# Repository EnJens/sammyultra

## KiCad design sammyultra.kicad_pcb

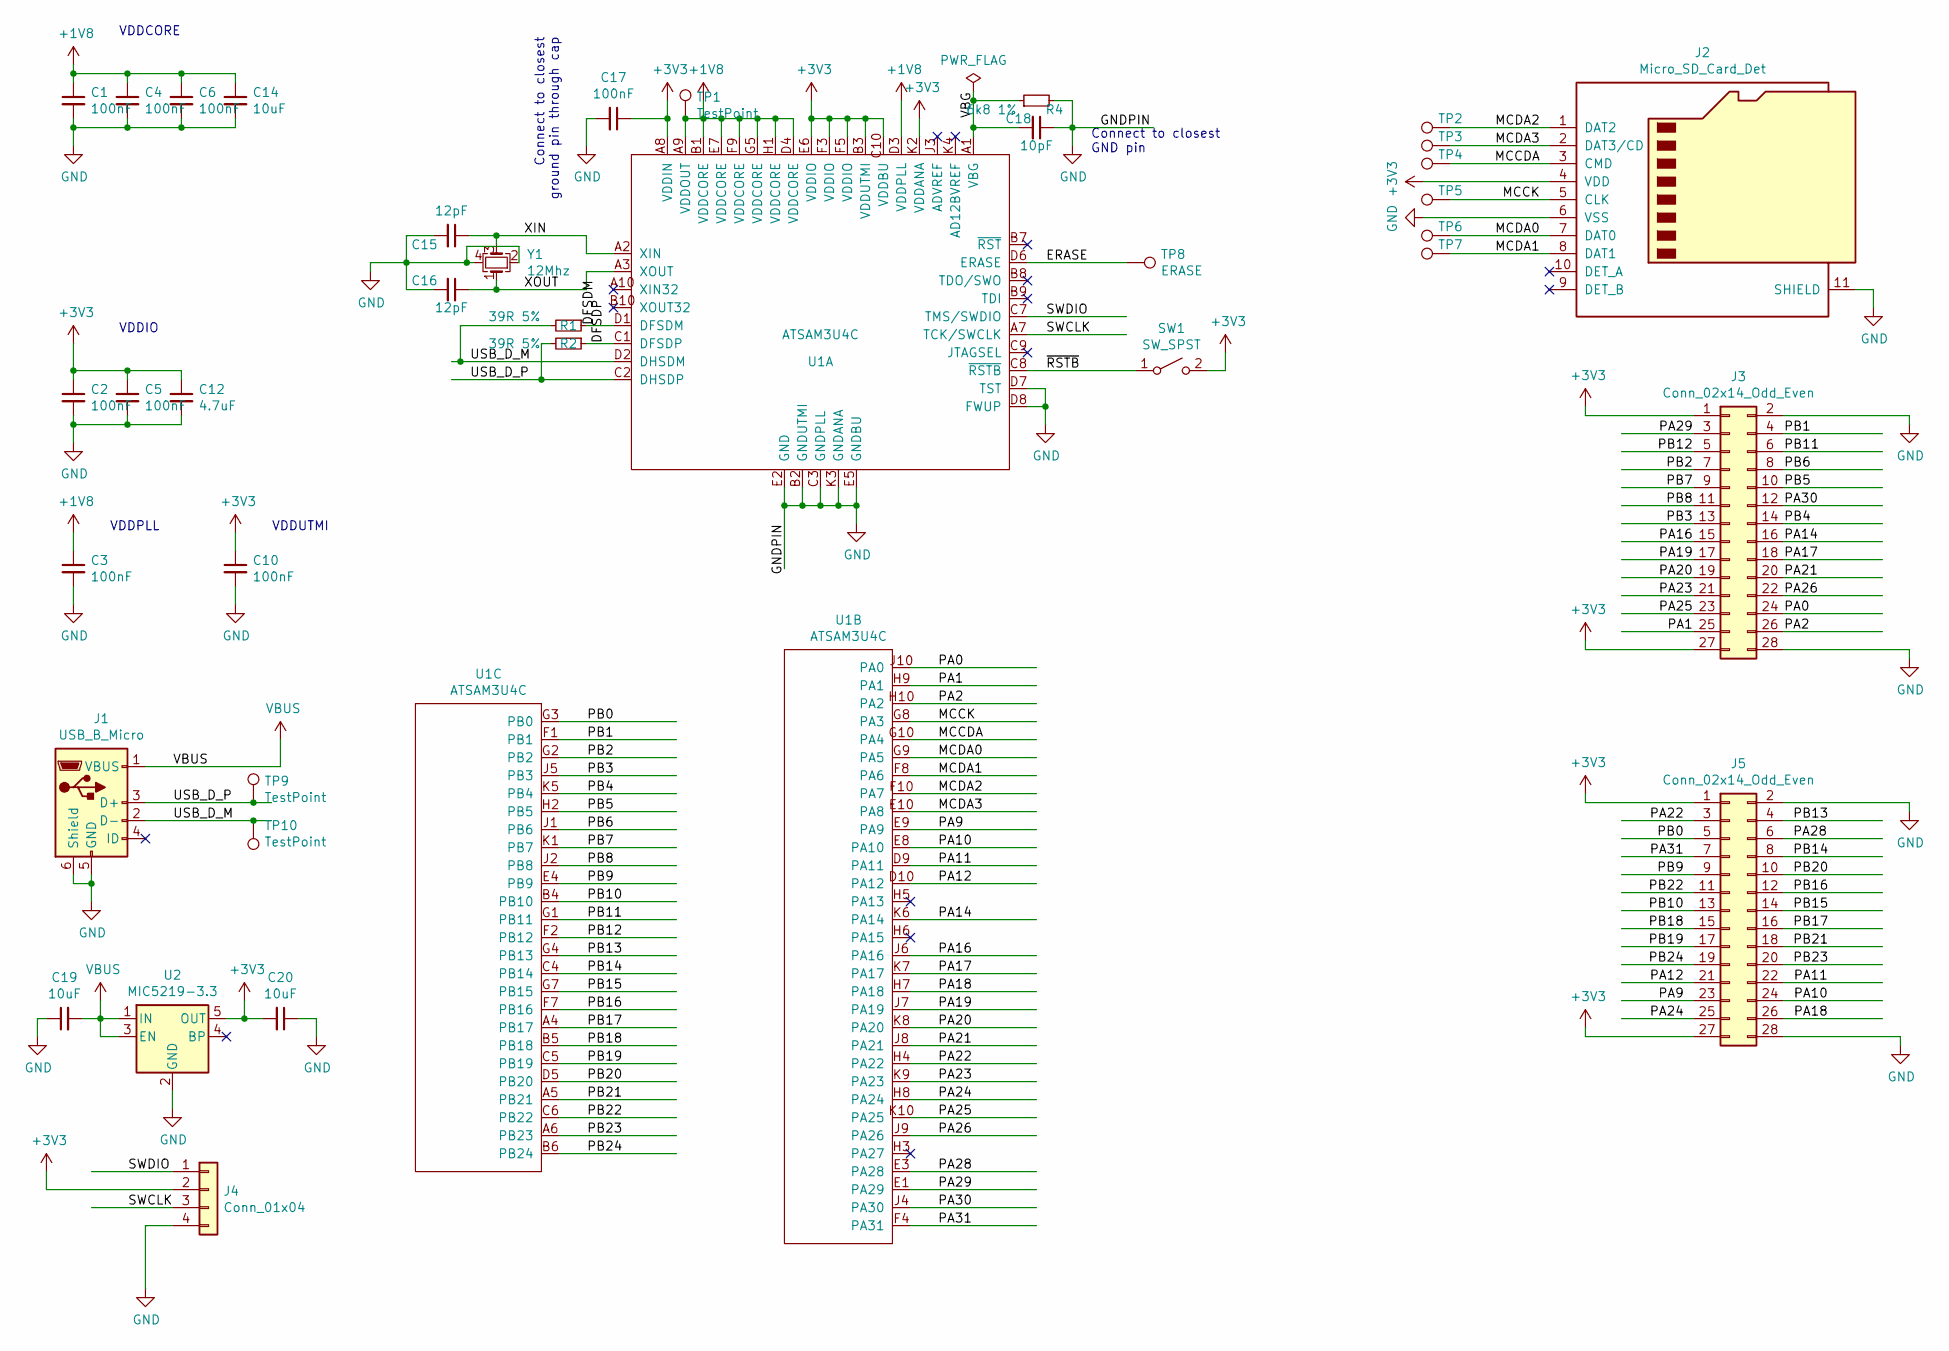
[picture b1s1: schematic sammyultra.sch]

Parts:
C1, C2, C3, C4, C5, C6, C10, C17: 100nF; C_0402_1005Metric
C12: 4.7uF; C_0603_1608Metric
C14, C19, C20: 10uF; C_0603_1608Metric
C15, C16: 12pF; C_0603_1608Metric
C18: 10pF; C_0402_1005Metric
J1: USB_B_Micro; USB_Micro-B_Molex-105017-0001
J2: Micro_SD_Card_Det; MOLEX_104031-0811
J3, J5: Conn_02x14_Odd_Even; PinHeader_2x14_P2.54mm_Vertical
J4: Conn_01x04; PinHeader_1x04_P1.27mm_Vertical
R1, R2: 39R 5%; R_0402_1005Metric
R4: 6k8 1%; R_0402_1005Metric
SW1: SW_SPST; SW_SPST_FSMSM
TP1, TP9, TP10: TestPoint; TestPoint_THTPad_D1.0mm_Drill0.5mm
TP2: MCDA2; TestPoint_Pad_D1.0mm
TP3: MCDA3; TestPoint_Pad_D1.0mm
TP4: MCCDA; TestPoint_Pad_D1.0mm
TP5: MCCK; TestPoint_Pad_D1.0mm
TP6: MCDA0; TestPoint_Pad_D1.0mm
TP7: MCDA1; TestPoint_Pad_D1.0mm
TP8: ERASE; TestPoint_THTPad_D1.0mm_Drill0.5mm
U1: ATSAM3U4C; BGA-100_10x10_9.0x9.0mm_Pitch_0.8mm_NSMD
U2: MIC5219-3.3; SOT-23-5
Y1: 12Mhz; Crystal_SMD_2520-4Pin_2.5x2.0mm

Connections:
+1V8: C1.1, C3.1, C4.1, C6.1, C14.1, TP1.1, U1.A9 (VDDOUT), U1.B1 (VDDCORE), U1.D3 (VDDPLL), U1.D4 (VDDCORE), U1.E7 (VDDCORE), U1.F9 (VDDCORE), U1.G5 (VDDCORE), U1.H1 (VDDCORE)
+3V3: C2.1, C5.1, C10.1, C12.1, C17.1, C20.2, J2.4 (VDD), J3.1, J3.27, J4.2, J5.1, J5.27, SW1.2 (B), U1.A8 (VDDIN), U1.B3 (VDDUTMI), U1.C10 (VDDBU), U1.E6 (VDDIO), U1.F3 (VDDIO), U1.F5 (VDDIO), U1.K2 (VDDANA), U2.5 (OUT)
/DFSDM: R1.1, U1.D1 (DFSDM)
/DFSDP: R2.1, U1.C1 (DFSDP)
/ERASE: TP8.1, U1.D6 (ERASE)
/MCCDA: J2.3 (CMD), TP4.1, U1.G10 (PA4)
/MCCK: J2.5 (CLK), TP5.1, U1.G8 (PA3)
/MCDA0: J2.7 (DAT0), TP6.1, U1.G9 (PA5)
/MCDA1: J2.8 (DAT1), TP7.1, U1.F8 (PA6)
/MCDA2: J2.1 (DAT2), TP2.1, U1.F10 (PA7)
/MCDA3: J2.2 (DAT3/CD), TP3.1, U1.E10 (PA8)
/PA0: J3.24, U1.J10 (PA0)
/PA1: J3.25, U1.H9 (PA1)
/PA2: J3.26, U1.H10 (PA2)
/PA9: J5.23, U1.E9 (PA9)
/PA10: J5.24, U1.E8 (PA10)
/PA11: J5.22, U1.D9 (PA11)
/PA12: J5.21, U1.D10 (PA12)
/PA14: J3.16, U1.K6 (PA14)
/PA16: J3.15, U1.J6 (PA16)
/PA17: J3.18, U1.K7 (PA17)
/PA18: J5.26, U1.H7 (PA18)
/PA19: J3.17, U1.J7 (PA19)
/PA20: J3.19, U1.K8 (PA20)
/PA21: J3.20, U1.J8 (PA21)
/PA22: J5.3, U1.H4 (PA22)
/PA23: J3.21, U1.K9 (PA23)
/PA24: J5.25, U1.H8 (PA24)
/PA25: J3.23, U1.K10 (PA25)
/PA26: J3.22, U1.J9 (PA26)
/PA28: J5.6, U1.E3 (PA28)
/PA29: J3.3, U1.E1 (PA29)
/PA30: J3.12, U1.J4 (PA30)
/PA31: J5.7, U1.F4 (PA31)
/PB0: J5.5, U1.G3 (PB0)
/PB1: J3.4, U1.F1 (PB1)
/PB2: J3.7, U1.G2 (PB2)
/PB3: J3.13, U1.J5 (PB3)
/PB4: J3.14, U1.K5 (PB4)
/PB5: J3.10, U1.H2 (PB5)
/PB6: J3.8, U1.J1 (PB6)
/PB7: J3.9, U1.K1 (PB7)
/PB8: J3.11, U1.J2 (PB8)
/PB9: J5.9, U1.E4 (PB9)
/PB10: J5.13, U1.B4 (PB10)
/PB11: J3.6, U1.G1 (PB11)
/PB12: J3.5, U1.F2 (PB12)
/PB13: J5.4, U1.G4 (PB13)
/PB14: J5.8, U1.C4 (PB14)
/PB15: J5.14, U1.G7 (PB15)
/PB16: J5.12, U1.F7 (PB16)
/PB17: J5.16, U1.A4 (PB17)
/PB18: J5.15, U1.B5 (PB18)
/PB19: J5.17, U1.C5 (PB19)
/PB20: J5.10, U1.D5 (PB20)
/PB21: J5.18, U1.A5 (PB21)
/PB22: J5.11, U1.C6 (PB22)
/PB23: J5.20, U1.A6 (PB23)
/PB24: J5.19, U1.B6 (PB24)
/SWCLK: J4.3, U1.A7 (TCK/SWCLK)
/SWDIO: J4.1, U1.C7 (TMS/SWDIO)
/USB_D_M: J1.2 (D-), R1.2, TP10.1, U1.D2 (DHSDM)
/USB_D_P: J1.3 (D+), R2.2, TP9.1, U1.C2 (DHSDP)
/VBG: C18.2, R4.1, U1.A1 (VBG)
/XIN: C15.1, U1.A2 (XIN), Y1.3
/XOUT: C16.1, U1.A3 (XOUT), Y1.1
/~RSTB~: SW1.1 (A), U1.C8 (~RSTB~)
GND: C1.2, C2.2, C3.2, C4.2, C5.2, C6.2, C10.2, C12.2, C14.2, C15.2, C16.2, C17.2, C18.1, C19.1, C20.1, J1.5 (GND), J1.6 (Shield), J2.6 (VSS), J2.11 (SHIELD), J3.2, J3.28, J4.4, J5.2, J5.28, R4.2, U1.B2 (GNDUTMI), U1.C3 (GNDPLL), U1.D7 (TST), U1.D8 (FWUP), U1.E2 (GND), U1.E5 (GNDBU), U1.F6 (GND), U1.G6 (GND), U1.K3 (GNDANA), U2.2 (GND), Y1.2, Y1.4
VBUS: C19.2, J1.1 (VBUS), U2.1 (IN), U2.3 (EN)

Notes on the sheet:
VDDCORE
VDDIO
VDDPLL
Connect to closest ground pin through cap
VDDUTMI
Connect to closest GND pin

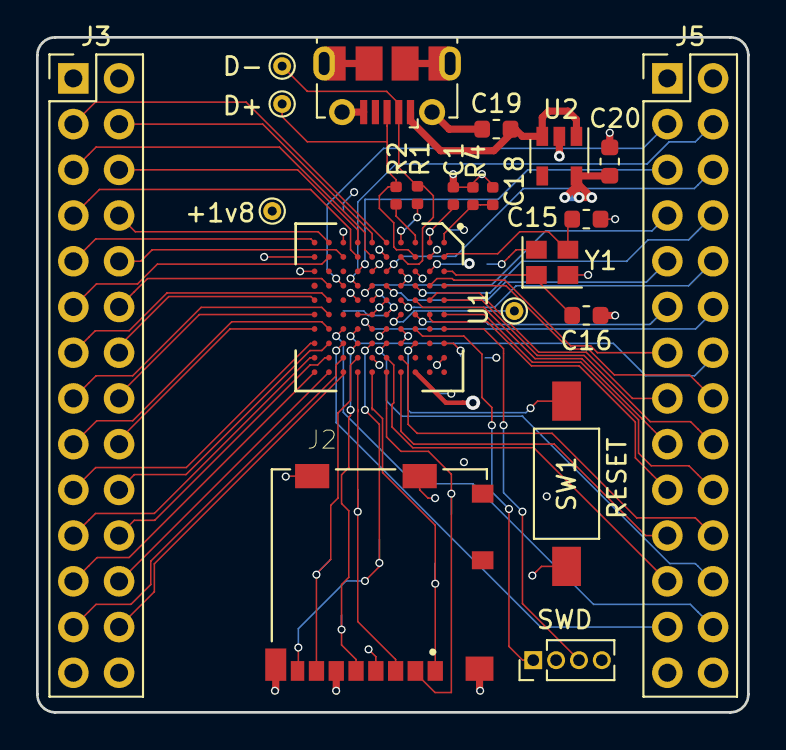
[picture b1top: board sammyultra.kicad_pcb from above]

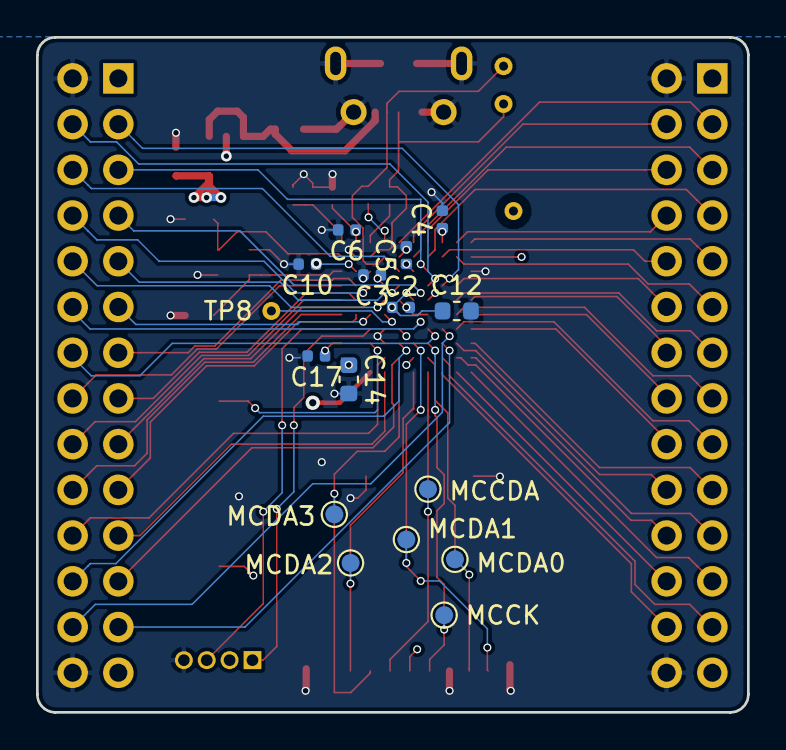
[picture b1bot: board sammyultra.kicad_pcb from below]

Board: 4 copper layers, 39.5 x 37.5 mm, 37 parts (15 on the bottom side), 69 nets.

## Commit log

2018-12-10 Board design revision A
2018-12-10 Add release gerbers
